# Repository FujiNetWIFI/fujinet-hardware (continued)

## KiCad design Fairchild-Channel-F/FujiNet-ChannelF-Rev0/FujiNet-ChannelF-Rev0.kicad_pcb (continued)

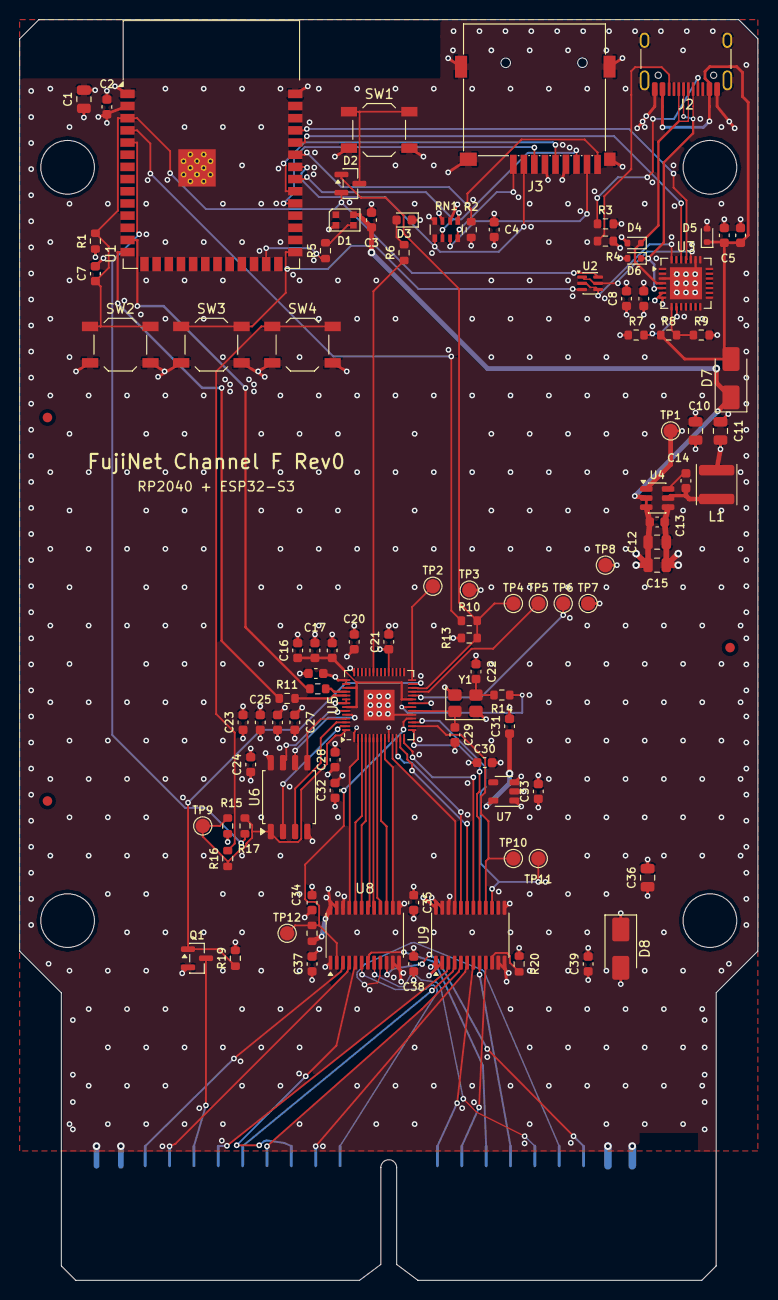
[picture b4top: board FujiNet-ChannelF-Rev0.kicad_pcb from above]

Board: 4 copper layers, 77.0 x 131.5 mm, 106 parts (0 on the bottom side), 87 nets.

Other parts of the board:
FID1, FID2, FID3: Fiducial_1mm_Mask2mm
H1, H2, H3, H4: MountingHole_5.6mm_NPTH

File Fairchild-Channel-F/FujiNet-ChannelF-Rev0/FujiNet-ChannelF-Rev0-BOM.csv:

"Qty","Refs","Value","Footprint","MPN","Manufacturer","LCSC","Description","DNP"
"6","C1,C10,C11,C12,C15,C36","22uF","C_0805_2012Metric","CL21A226MAQNNNE","Samsung Electro-Mechanics","C45783","capacitor (several uses: see schematic)",""
"22","C2,C3,C6,C9,C13,C14,C16,C17,C20,C21,C24,C25,C26,C27,C28,C31,C32,C34,C35,C37,C38,C39","100nF","C_0603_1608Metric","CC0603KRX7R9BB104","YAGEO","C14663","capacitor (several uses: see schematic)",""
"2","C4,C23","10uF","C_0603_1608Metric","CL10A106KP8NNNC","Samsung Electro-Mechanics","C19702","capacitor (several uses: see schematic)",""
"6","C5,C7,C18,C19,C30,C33","1uF","C_0603_1608Metric","CL10A105KB8NNNC","Samsung Electro-Mechanics","C15849","capacitor (several uses: see schematic)",""
"1","C8","4.7uF","C_0603_1608Metric","CL10A475KO8NNNC","Samsung Electro-Mechanics","C19666","CP2102N VDD bulk",""
"2","C22,C29","15pF","C_0603_1608Metric","CL10C150JB8NNNC","Samsung Electro-Mechanics","C1644","crystal load",""
"1","D1","WS2812B-2020-V6","LED_WS2812B-2020_PLCC4_2.0x2.0mm","WS2812B-2020-V6","Worldsemi","C52917434","status LED on +5V (datasheet VDD 3.7-5.3 V; VIH 2.7 V takes 3.3 V data)",""
"1","D2","BAT54C","SOT-23","BAT54C,215","Nexperia","C37704","RESET steering, common cathode",""
"1","D3","green","LED_0603_1608Metric","KT-0603G","Hubei KENTO Elec","C12624","RP activity LED",""
"3","D4,D5,D6","ESD5Z5.0T1G","D_SOD-523","ESD5Z5.0T1G","onsemi","C82044","ESD",""
"2","D7,D8","SS34","D_SMA","SS34","MDD (Microdiode Semiconductor)","C8678","diode (several uses: see schematic)",""
"1","J2","USB-C","USB_C_Receptacle_HRO_TYPE-C-31-M-12","TYPE-C-31-M-12","Korean Hroparts Elec","C165948","power + S3 programming",""
"1","J3","microSD","TF-SMD_TF-015","TF-015","SOFNG","C113206","microSD push-push, SPI mode",""
"1","L1","6.8uH","L_Sunlord_SWPA4030S","SWPA4030S6R8MT","Sunlord","C62684","buck inductor",""
"1","Q1","2N7002","SOT-23","2N7002","Jiangsu Changjing (JSCJ)","C8545","/INTREQ open-drain driver (GP16, unused by the firmware)",""
"6","R1,R2,R7,R13,R15,R20","10k","R_0603_1608Metric","0603WAF1002T5E","UNI-ROYAL","C25804","resistor (several uses: see schematic)",""
"2","R3,R4","5.1k","R_0603_1608Metric","0603WAF5101T5E","UNI-ROYAL","C23186","UFP Rd",""
"2","R5,R6","330R","R_0603_1608Metric","0603WAF3300T5E","UNI-ROYAL","C23138","resistor (several uses: see schematic)",""
"1","R8","22k","R_0603_1608Metric","0603WAF2202T5E","UNI-ROYAL","C31850","VBUS sense divider",""
"1","R9","47k","R_0603_1608Metric","0603WAF4702T5E","UNI-ROYAL","C25819","VBUS sense divider",""
"4","R10,R14,R16,R17","1k","R_0603_1608Metric","0603WAF1001T5E","UNI-ROYAL","C21190","resistor (several uses: see schematic)",""
"2","R11,R12","27R","R_0603_1608Metric","0603WAF270JT5E","UNI-ROYAL","C25190","USB series",""
"1","R18","4.7k","R_0603_1608Metric","0603WAF4701T5E","UNI-ROYAL","C23162","DIR pull-up: console -> cart through RP reset / boot",""
"1","R19","100k","R_0603_1608Metric","0603WAF1003T5E","UNI-ROYAL","C25803","/INTREQ FET gate pull-down",""
"1","RN1","4x10k","R_Array_Convex_4x0603","4D03WGJ0103T5E","UNI-ROYAL","C29718","SD pull-ups",""
"1","SW1","RESET","SW_SPST_TL3342","TL3342F160QG","E-Switch","C2886898","cart RESET: RP RUN + S3 EN via BAT54C",""
"1","SW2","S3_RST","SW_SPST_TL3342","TL3342F160QG","E-Switch","C2886898","ESP32-S3 EN",""
"1","SW3","S3_BOOT","SW_SPST_TL3342","TL3342F160QG","E-Switch","C2886898","ESP32-S3 BOOT (IO0)",""
"1","SW4","BOOTSEL","SW_SPST_TL3342","TL3342F160QG","E-Switch","C2886898","RP2040 BOOTSEL (hold while pressing RESET)",""
"1","U1","ESP32-S3-WROOM-1-N16R8","ESP32-S3-WROOM-1","ESP32-S3-WROOM-1-N16R8","Espressif","C2913202","FujiNet core (fujiversal-channelf)",""
"1","U2","UMH3N","SOT-363_SC-70-6","UMH3N","Jiangsu Changjing (JSCJ)","C62892","esptool auto-program (DevKitC-1 style)",""
"1","U3","CP2102N-A02-GQFN28","QFN-28-1EP_5x5mm_P0.5mm_EP3.35x3.35mm","CP2102N-A02-GQFN28R","Silicon Labs","C964632","USB-UART for S3 flashing/console (self-powered)",""
"1","U4","AP63203WU","TSOT-23-6","AP63203WU-7","Diodes Incorporated","C780769","3.3V 2A buck",""
"1","U5","RP2040","QFN-56-1EP_7x7mm_P0.4mm_EP3.2x3.2mm","RP2040","Raspberry Pi","C2040","F8 bus memory device: ROMC state machine on core1 (fujichannelf)",""
"1","U6","W25Q16JVSSIQ","SOIC-8_5.3x5.3mm_P1.27mm","W25Q16JVSSIQ","Winbond","C82317","2 MB QSPI boot flash",""
"1","U7","AP2112K-3.3","SOT-23-5","AP2112K-3.3TRG1","Diodes Incorporated","C51118","RP2040 + flash + translator B ports 3.3V LDO, fast start",""
"2","U8,U9","SN74LVC4245APWR","TSSOP-24_4.4x7.8mm_P0.65mm","SN74LVC4245APWR","Texas Instruments","C7859","U (several uses: see schematic)",""
"1","Y1","12MHz","Crystal_SMD_3225-4Pin_3.2x2.5mm","ABM8-272-T3","Abracon","C20625731","",""

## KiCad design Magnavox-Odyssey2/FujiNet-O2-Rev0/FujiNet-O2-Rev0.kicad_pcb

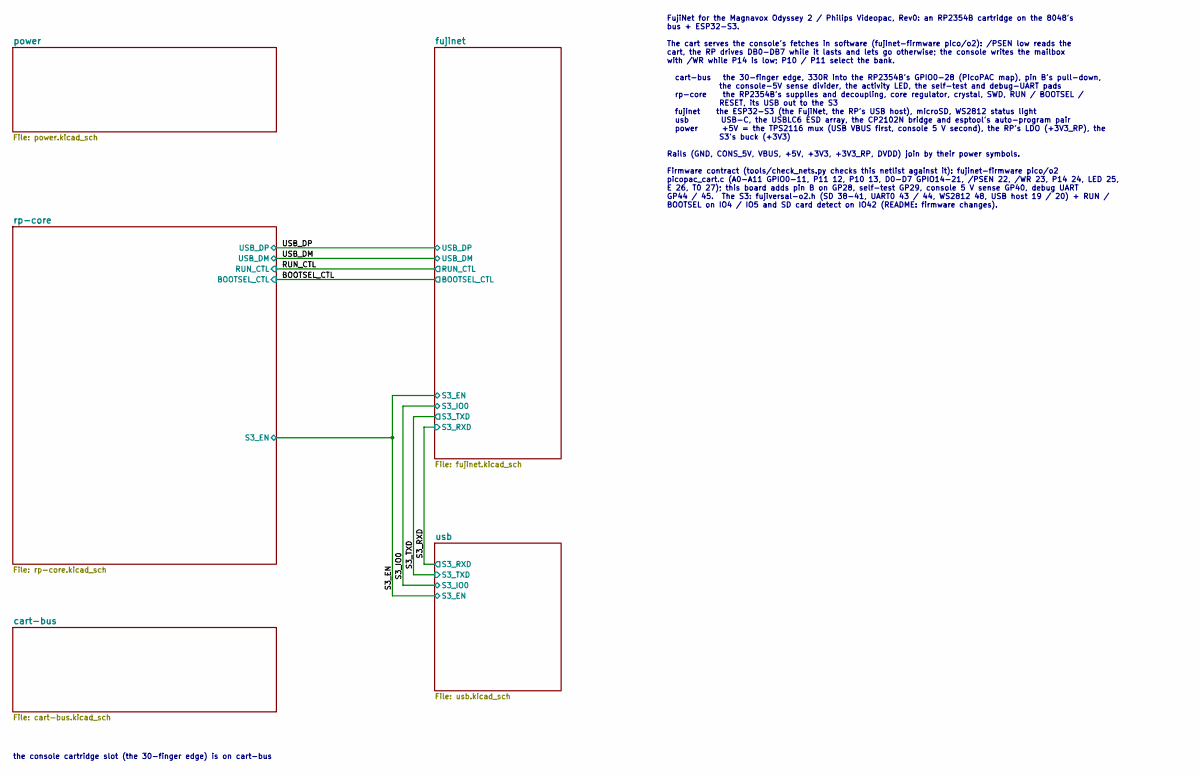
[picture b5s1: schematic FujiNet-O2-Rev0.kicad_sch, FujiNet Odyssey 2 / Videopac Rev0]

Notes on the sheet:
the console cartridge slot (the 30-finger edge) is on cart-bus
FujiNet for the Magnavox Odyssey 2 / Philips Videopac, Rev0: an RP2354B cartridge on the 8048's bus + ESP32-S3. The cart serves the console's fetches in software (fujinet-firmware pico/o2): /PSEN low reads the cart, the RP drives DB0-DB7 while it lasts and lets go otherwise; the console writes the 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

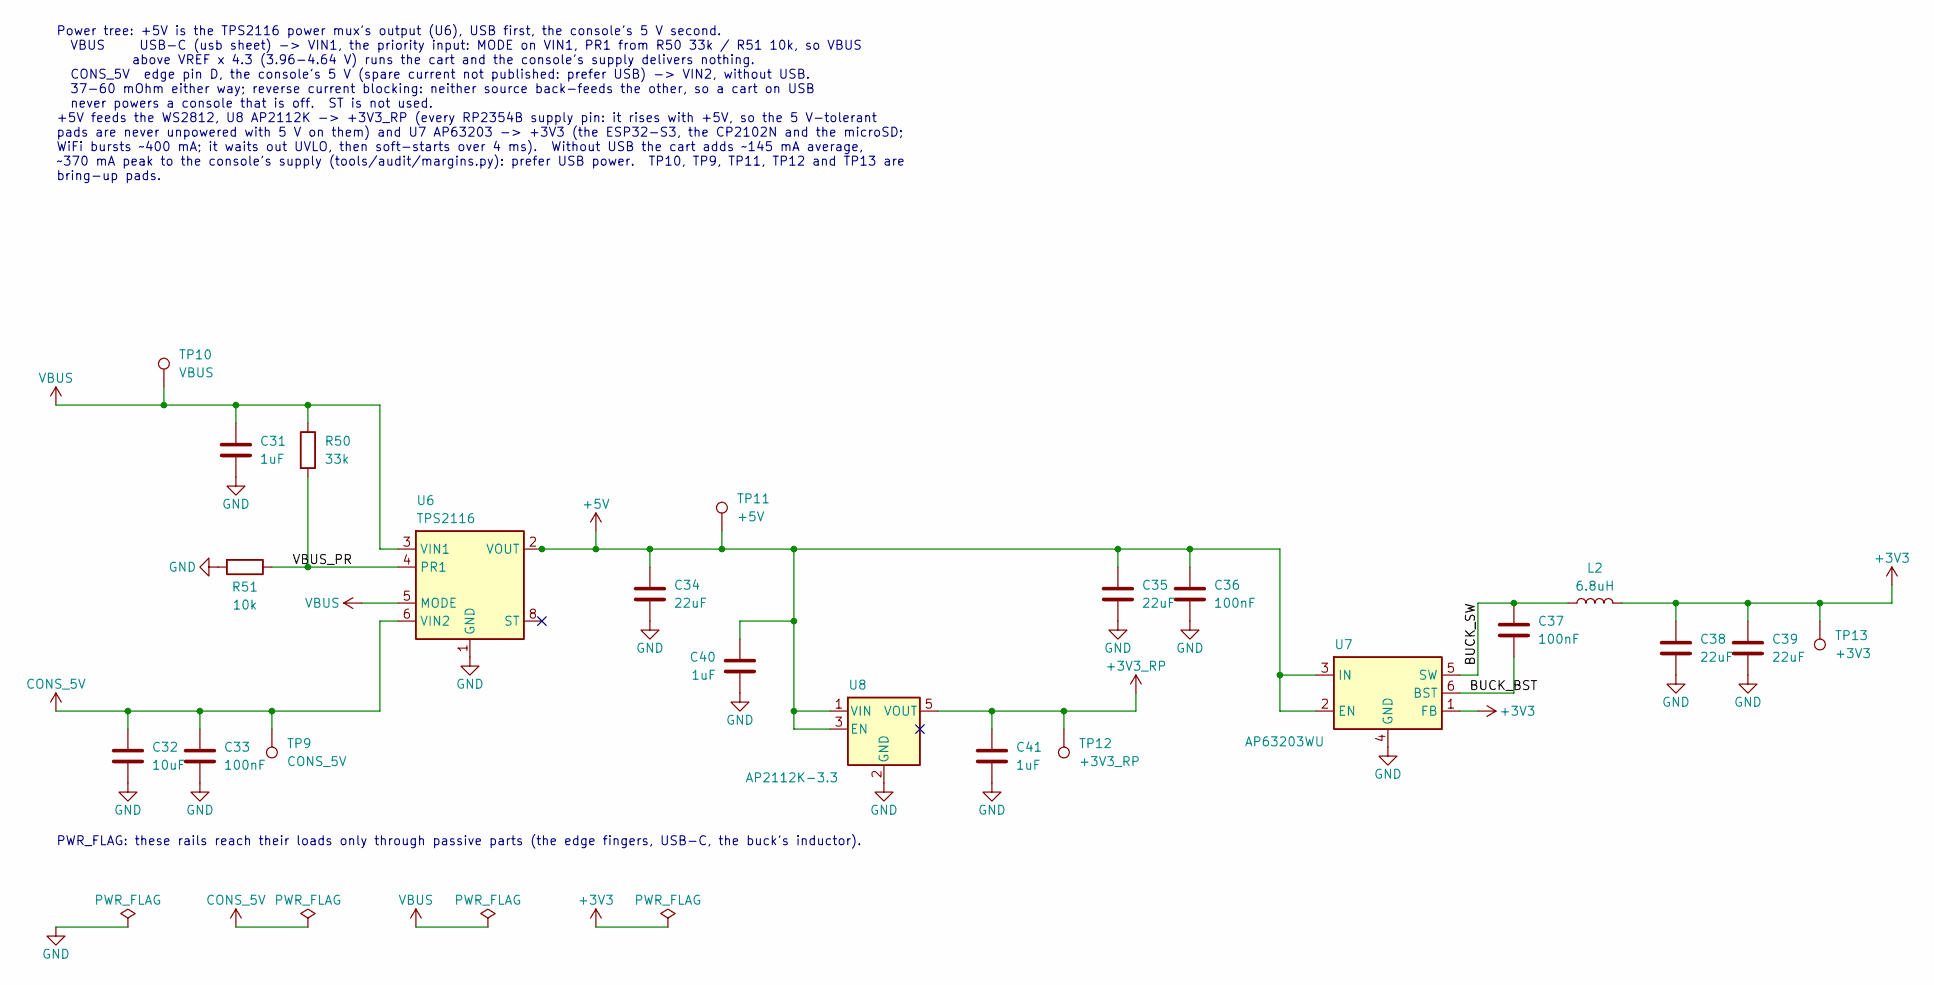
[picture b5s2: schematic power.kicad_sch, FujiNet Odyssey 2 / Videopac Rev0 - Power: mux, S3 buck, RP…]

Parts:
C31, C40, C41: 1uF; C_0603_1608Metric; MPN CL10A105KB8NNNC; LCSC C15849
C32: 10uF; C_0603_1608Metric; MPN CL10A106KP8NNNC; LCSC C19702
C33, C36, C37: 100nF; C_0603_1608Metric; MPN CC0603KRX7R9BB104; LCSC C14663
C34, C35, C38, C39: 22uF; C_0805_2012Metric; MPN CL21A226MAQNNNE; LCSC C45783
L2: 6.8uH; L_Sunlord_SWPA4030S; MPN SWPA4030S6R8MT; LCSC C62684
R50: 33k; R_0603_1608Metric; MPN 0603WAF3302T5E; LCSC C4216
R51: 10k; R_0603_1608Metric; MPN 0603WAF1002T5E; LCSC C25804
TP9: CONS_5V; TestPoint_Pad_D1.5mm
TP10: VBUS; TestPoint_Pad_D1.5mm
TP11: +5V; TestPoint_Pad_D1.5mm
TP12: +3V3_RP; TestPoint_Pad_D1.5mm
TP13: +3V3; TestPoint_Pad_D1.5mm
U6: TPS2116; SOT-583-8; MPN TPS2116DRLR; LCSC C3235557
U7: AP63203WU; TSOT-23-6; MPN AP63203WU-7; LCSC C780769
U8: AP2112K-3.3; SOT-23-5; MPN AP2112K-3.3TRG1; LCSC C51118

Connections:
+3V3: C38.1, C39.1, L2.2, TP13.1, U7.1 (FB); also elsewhere on the board
+3V3_RP: C41.1, TP12.1, U8.5 (VOUT); also elsewhere on the board
+5V: C34.1, C35.1, C36.1, C40.1, TP11.1, U6.2 (VOUT), U6.7 (VOUT), U7.2 (EN), U7.3 (IN), U8.1 (VIN), U8.3 (EN); also elsewhere on the board
/power/BUCK_BST: C37.2, U7.6 (BST)
/power/BUCK_SW: C37.1, L2.1, U7.5 (SW)
/power/VBUS_PR: R50.2, R51.1, U6.4 (PR1)
CONS_5V: C32.1, C33.1, TP9.1, U6.6 (VIN2); also elsewhere on the board
GND: C31.2, C32.2, C33.2, C34.2, C35.2, C36.2, C38.2, C39.2, C40.2, C41.2, R51.2, U6.1 (GND), U7.4 (GND), U8.2 (GND); also elsewhere on the board
VBUS: C31.1, R50.1, TP10.1, U6.3 (VIN1), U6.5 (MODE); also elsewhere on the board

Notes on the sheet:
PWR_FLAG: these rails reach their loads only through passive parts (the edge fingers, USB-C, the buck's inductor).
Power tree: +5V is the TPS2116 power mux's output (U6), USB first, the console's 5 V second. VBUS USB-C (usb sheet) -> VIN1, the priority input: MODE on VIN1, PR1 from R50 33k / R51 10k, so VBUS above VREF x 4.3 (3.96-4.64 V) runs the cart and the console's supply delivers nothing. CONS_5V edge pin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

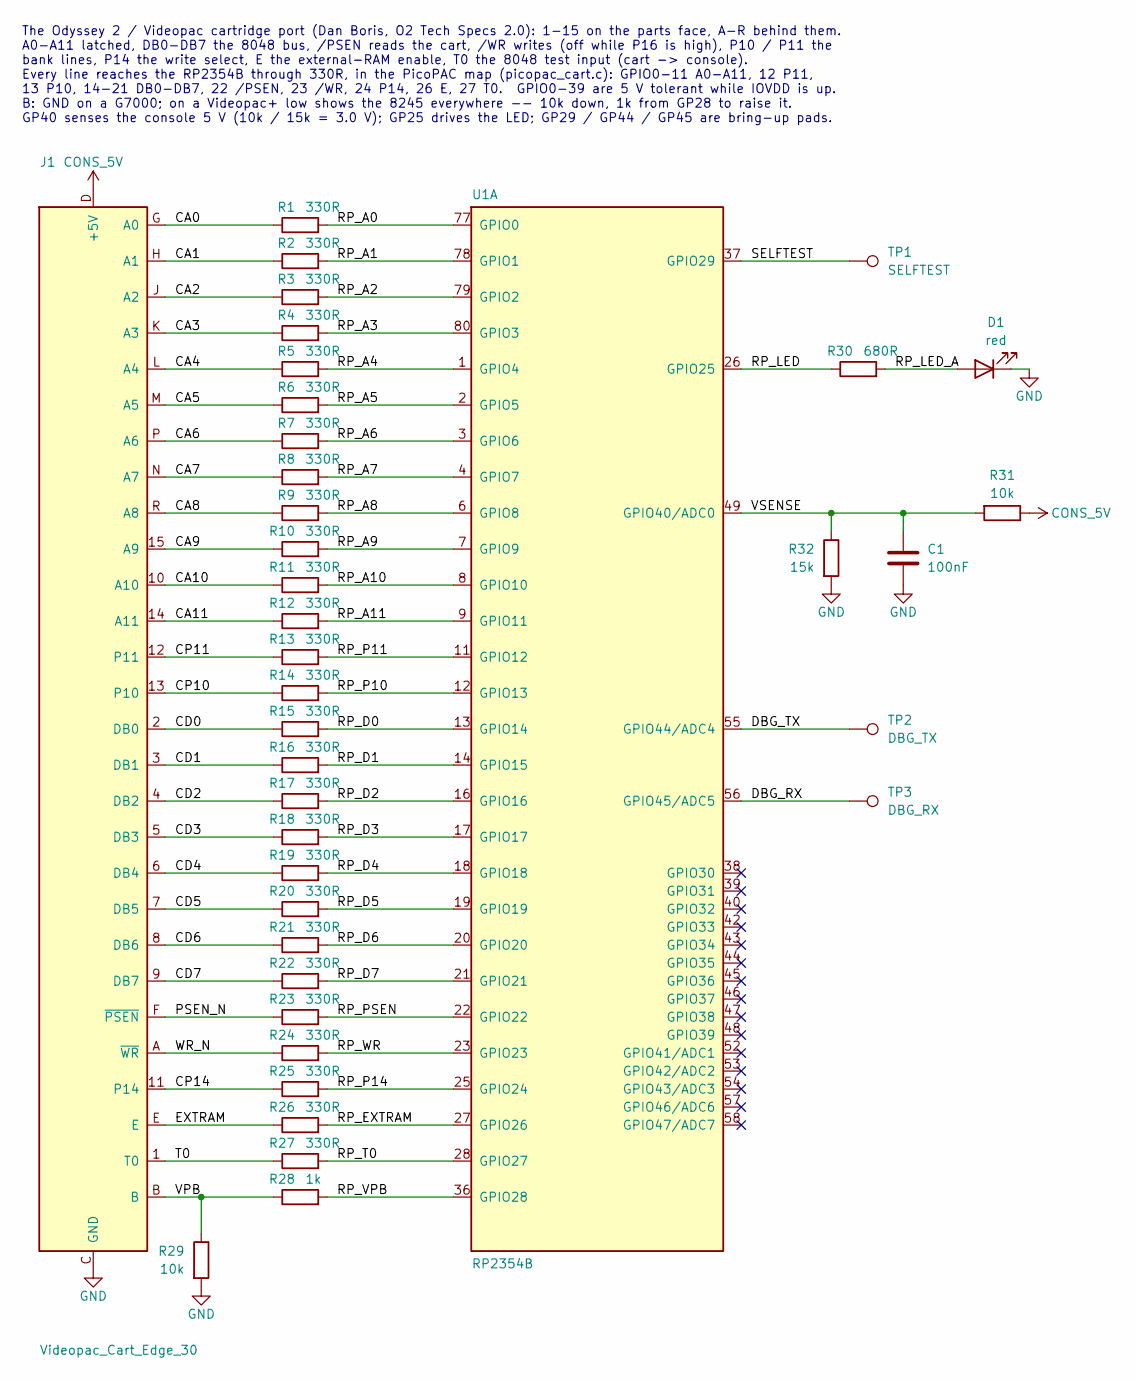
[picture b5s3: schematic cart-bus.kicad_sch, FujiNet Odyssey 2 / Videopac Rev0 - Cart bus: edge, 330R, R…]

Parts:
C1: 100nF; C_0603_1608Metric; MPN CC0603KRX7R9BB104; LCSC C14663
D1: red; LED_0603_1608Metric; MPN KT-0603R; LCSC C2286
J1: Videopac_Cart_Edge_30
R1, R2, R3, R4, R5, R6, R7, R8, R9, R10, R11, R12, R13, R14, R15, R16, R17, R18, R19, R20, R21, R22, R23, R24, R25, R26, R27: 330R; R_0603_1608Metric; MPN 0603WAF3300T5E; LCSC C23138
R28: 1k; R_0603_1608Metric; MPN 0603WAF1001T5E; LCSC C21190
R29, R31: 10k; R_0603_1608Metric; MPN 0603WAF1002T5E; LCSC C25804
R30: 680R; R_0603_1608Metric; MPN 0603WAF6800T5E; LCSC C23228
R32: 15k; R_0603_1608Metric; MPN 0603WAF1502T5E; LCSC C22809
TP1: SELFTEST; TestPoint_Pad_D1.5mm
TP2: DBG_TX; TestPoint_Pad_D1.5mm
TP3: DBG_RX; TestPoint_Pad_D1.5mm
U1: RP2354B; QFN-80-1EP_10x10mm_P0.4mm_EP3.4x3.4mm; MPN RP2354B; LCSC C39843328

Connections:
/cart-bus/CA0: J1.G (A0), R1.1
/cart-bus/CA1: J1.H (A1), R2.1
/cart-bus/CA2: J1.J (A2), R3.1
/cart-bus/CA3: J1.K (A3), R4.1
/cart-bus/CA4: J1.L (A4), R5.1
/cart-bus/CA5: J1.M (A5), R6.1
/cart-bus/CA6: J1.P (A6), R7.1
/cart-bus/CA7: J1.N (A7), R8.1
/cart-bus/CA8: J1.R (A8), R9.1
/cart-bus/CA9: J1.15 (A9), R10.1
/cart-bus/CA10: J1.10 (A10), R11.1
/cart-bus/CA11: J1.14 (A11), R12.1
/cart-bus/CD0: J1.2 (DB0), R15.1
/cart-bus/CD1: J1.3 (DB1), R16.1
/cart-bus/CD2: J1.4 (DB2), R17.1
/cart-bus/CD3: J1.5 (DB3), R18.1
/cart-bus/CD4: J1.6 (DB4), R19.1
/cart-bus/CD5: J1.7 (DB5), R20.1
/cart-bus/CD6: J1.8 (DB6), R21.1
/cart-bus/CD7: J1.9 (DB7), R22.1
/cart-bus/CP10: J1.13 (P10), R14.1
/cart-bus/CP11: J1.12 (P11), R13.1
/cart-bus/CP14: J1.11 (P14), R25.1
/cart-bus/DBG_RX: TP3.1, U1.56 (GPIO45/ADC5)
/cart-bus/DBG_TX: TP2.1, U1.55 (GPIO44/ADC4)
/cart-bus/EXTRAM: J1.E, R26.1
/cart-bus/PSEN_N: J1.F (~PSEN), R23.1
/cart-bus/RP_A0: R1.2, U1.77 (GPIO0)
/cart-bus/RP_A1: R2.2, U1.78 (GPIO1)
/cart-bus/RP_A2: R3.2, U1.79 (GPIO2)
/cart-bus/RP_A3: R4.2, U1.80 (GPIO3)
/cart-bus/RP_A4: R5.2, U1.1 (GPIO4)
/cart-bus/RP_A5: R6.2, U1.2 (GPIO5)
/cart-bus/RP_A6: R7.2, U1.3 (GPIO6)
/cart-bus/RP_A7: R8.2, U1.4 (GPIO7)
/cart-bus/RP_A8: R9.2, U1.6 (GPIO8)
/cart-bus/RP_A9: R10.2, U1.7 (GPIO9)
/cart-bus/RP_A10: R11.2, U1.8 (GPIO10)
/cart-bus/RP_A11: R12.2, U1.9 (GPIO11)
/cart-bus/RP_D0: R15.2, U1.13 (GPIO14)
/cart-bus/RP_D1: R16.2, U1.14 (GPIO15)
/cart-bus/RP_D2: R17.2, U1.16 (GPIO16)
/cart-bus/RP_D3: R18.2, U1.17 (GPIO17)
/cart-bus/RP_D4: R19.2, U1.18 (GPIO18)
/cart-bus/RP_D5: R20.2, U1.19 (GPIO19)
/cart-bus/RP_D6: R21.2, U1.20 (GPIO20)
/cart-bus/RP_D7: R22.2, U1.21 (GPIO21)
/cart-bus/RP_EXTRAM: R26.2, U1.27 (GPIO26)
/cart-bus/RP_LED: R30.1, U1.26 (GPIO25)
/cart-bus/RP_LED_A: D1.2 (A), R30.2
/cart-bus/RP_P10: R14.2, U1.12 (GPIO13)
/cart-bus/RP_P11: R13.2, U1.11 (GPIO12)
/cart-bus/RP_P14: R25.2, U1.25 (GPIO24)
/cart-bus/RP_PSEN: R23.2, U1.22 (GPIO22)
/cart-bus/RP_T0: R27.2, U1.28 (GPIO27)
/cart-bus/RP_VPB: R28.2, U1.36 (GPIO28)
/cart-bus/RP_WR: R24.2, U1.23 (GPIO23)
/cart-bus/SELFTEST: TP1.1, U1.37 (GPIO29)
/cart-bus/T0: J1.1 (T0), R27.1
/cart-bus/VPB: J1.B, R28.1, R29.1
/cart-bus/VSENSE: C1.1, R31.2, R32.1, U1.49 (GPIO40/ADC0)
/cart-bus/WR_N: J1.A (~WR), R24.1
CONS_5V: J1.D (+5V), R31.1; also elsewhere on the board
GND: C1.2, D1.1 (K), J1.C (GND), R29.2, R32.2; also elsewhere on the board

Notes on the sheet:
The Odyssey 2 / Videopac cartridge port (Dan Boris, O2 Tech Specs 2.0): 1-15 on the parts face, A-R behind them. A0-A11 latched, DB0-DB7 the 8048 bus, /PSEN reads the cart, /WR writes (off while P16 is high), P10 / P11 the bank lines, P14 the write select, E the external-RAM enable, T0 the 8048 tes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

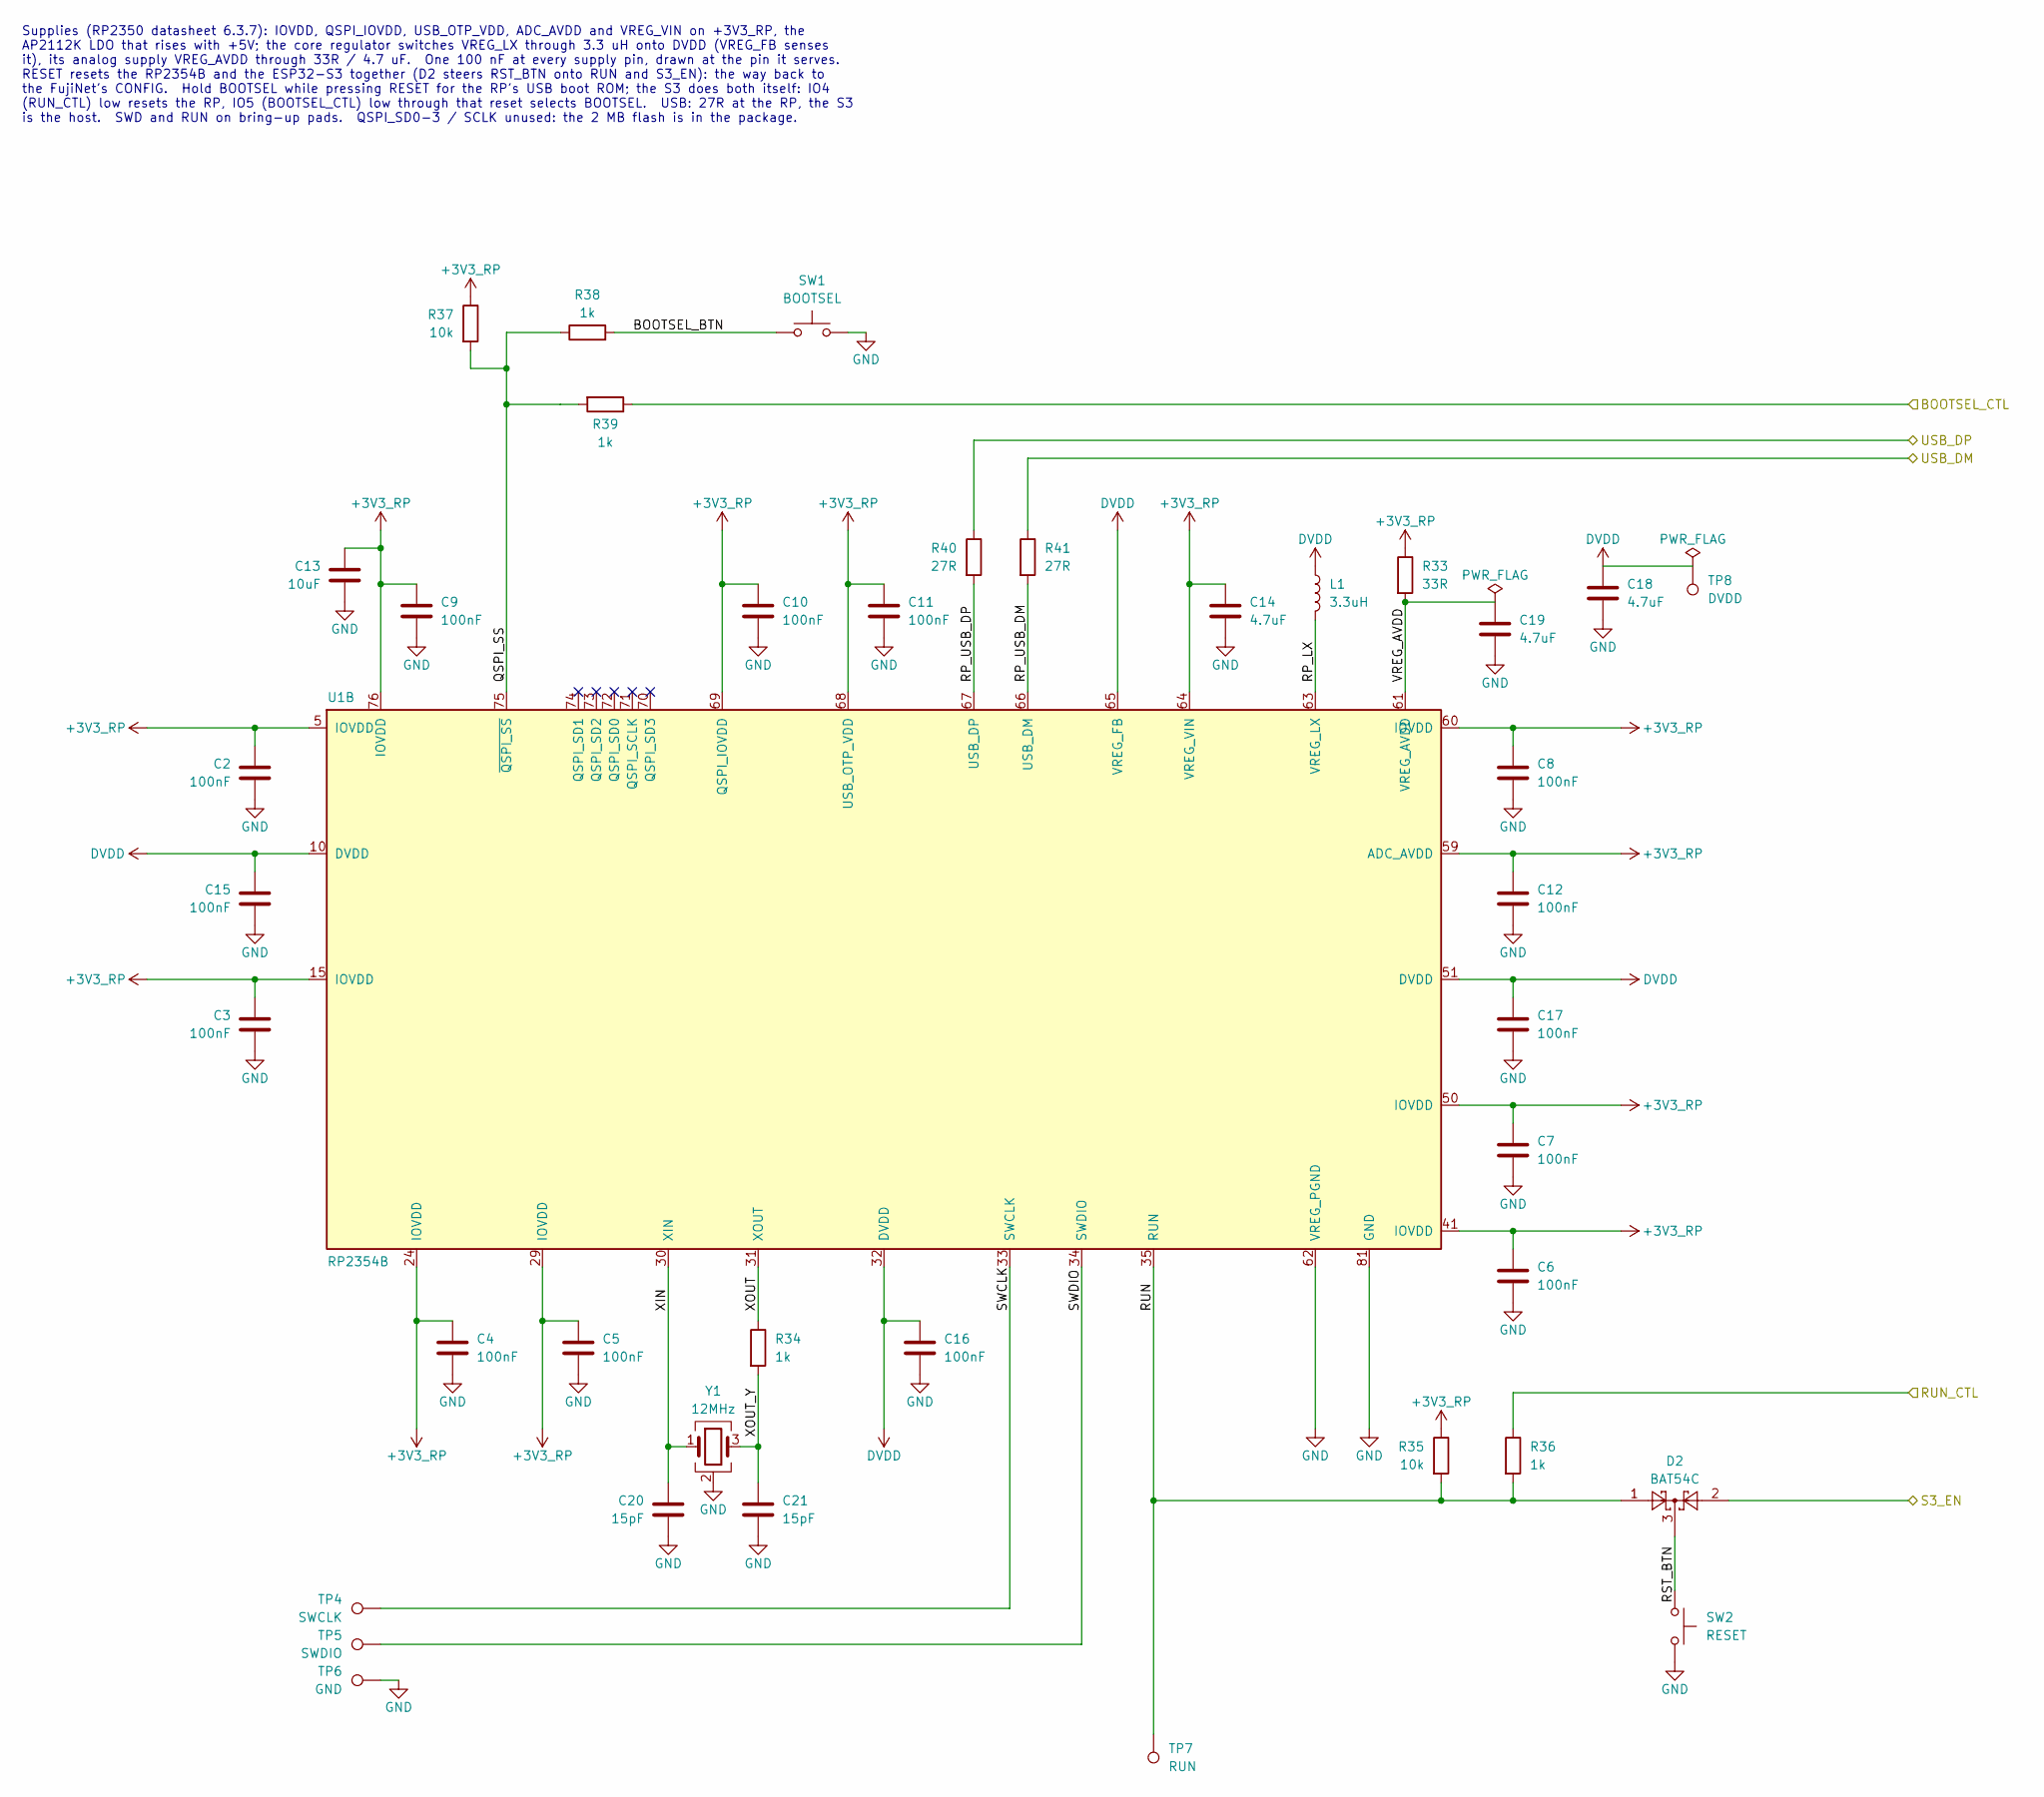
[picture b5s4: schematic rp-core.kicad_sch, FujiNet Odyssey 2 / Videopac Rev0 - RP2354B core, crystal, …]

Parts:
C2, C3, C4, C5, C6, C8, C9, C10, C12, C15, C16: 100nF; C_0603_1608Metric; MPN CC0603KRX7R9BB104; LCSC C14663
C7, C11, C17: 100nF; RPI_C0402; MPN CL05B104KO5NNNC; LCSC C1525
C13: 10uF; C_0603_1608Metric; MPN CL10A106KP8NNNC; LCSC C19702
C14, C18: 4.7uF; RPI_C0402_wide; MPN CL05A475MP5NRNC; LCSC C23733
C19: 4.7uF; RPI_C0402; MPN CL05A475MP5NRNC; LCSC C23733
C20, C21: 15pF; C_0603_1608Metric; MPN CL10C150JB8NNNC; LCSC C1644
D2: BAT54C; SOT-23; MPN BAT54C,215; LCSC C37704
L1: 3.3uH; RPI_L_AOTA-B201610S3R3; MPN AOTA-B201610S3R3-101-T; LCSC C42411119
R33: 33R; RPI_R0402; MPN 0402WGF330JTCE; LCSC C25105
R34, R36, R38, R39: 1k; R_0603_1608Metric; MPN 0603WAF1001T5E; LCSC C21190
R35, R37: 10k; R_0603_1608Metric; MPN 0603WAF1002T5E; LCSC C25804
R40, R41: 27R; RPI_R0402; MPN 0402WGF270JTCE; LCSC C25100
SW1: BOOTSEL; SW_SPST_TS-1187A; MPN TS-1187A-B-A-B; LCSC C318884
SW2: RESET; SW_SPST_TS-1187A; MPN TS-1187A-B-A-B; LCSC C318884
TP4: SWCLK; TestPoint_Pad_D1.5mm
TP5: SWDIO; TestPoint_Pad_D1.5mm
TP6: GND; TestPoint_Pad_D1.5mm
TP7: RUN; TestPoint_Pad_D1.5mm
TP8: DVDD; TestPoint_Pad_D1.5mm
U1: RP2354B; QFN-80-1EP_10x10mm_P0.4mm_EP3.4x3.4mm; MPN RP2354B; LCSC C39843328
Y1: 12MHz; Crystal_SMD_3225-4Pin_3.2x2.5mm; MPN ABM8-272-T3; LCSC C20625731

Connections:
+3V3_RP: C2.1, C3.1, C4.1, C5.1, C6.1, C7.1, C8.1, C9.1, C10.1, C11.1, C12.1, C13.1, C14.1, R33.1, R35.1, R37.1, U1.5 (IOVDD), U1.15 (IOVDD), U1.24 (IOVDD), U1.29 (IOVDD), U1.41 (IOVDD), U1.50 (IOVDD), U1.59 (ADC_AVDD), U1.60 (IOVDD), U1.64 (VREG_VIN), U1.68 (USB_OTP_VDD), U1.69 (QSPI_IOVDD), U1.76 (IOVDD); also elsewhere on the board
/BOOTSEL_CTL: R39.1; also elsewhere on the board
/RUN_CTL: R36.1; also elsewhere on the board
/S3_EN: D2.2; also elsewhere on the board
/USB_DM: R41.1; also elsewhere on the board
/USB_DP: R40.1; also elsewhere on the board
/rp-core/BOOTSEL_BTN: R38.2, SW1.1
/rp-core/QSPI_SS: R37.2, R38.1, R39.2, U1.75 (~QSPI_SS)
/rp-core/RP_LX: L1.2, U1.63 (VREG_LX)
/rp-core/RP_USB_DM: R41.2, U1.66 (USB_DM)
/rp-core/RP_USB_DP: R40.2, U1.67 (USB_DP)
/rp-core/RST_BTN: D2.3, SW2.1
/rp-core/RUN: D2.1, R35.2, R36.2, TP7.1, U1.35 (RUN)
/rp-core/SWCLK: TP4.1, U1.33 (SWCLK)
/rp-core/SWDIO: TP5.1, U1.34 (SWDIO)
/rp-core/VREG_AVDD: C19.1, R33.2, U1.61 (VREG_AVDD)
/rp-core/XIN: C20.1, U1.30 (XIN), Y1.1
/rp-core/XOUT: R34.1, U1.31 (XOUT)
/rp-core/XOUT_Y: C21.1, R34.2, Y1.3
DVDD: C15.1, C16.1, C17.1, C18.1, L1.1, TP8.1, U1.10 (DVDD), U1.32 (DVDD), U1.51 (DVDD), U1.65 (VREG_FB)
GND: C2.2, C3.2, C4.2, C5.2, C6.2, C7.2, C8.2, C9.2, C10.2, C11.2, C12.2, C13.2, C14.2, C15.2, C16.2, C17.2, C18.2, C19.2, C20.2, C21.2, SW1.2, SW2.2, TP6.1, U1.62 (VREG_PGND), U1.81 (GND), Y1.2 (G), Y1.4 (G); also elsewhere on the board

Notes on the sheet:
Supplies (RP2350 datasheet 6.3.7): IOVDD, QSPI_IOVDD, USB_OTP_VDD, ADC_AVDD and VREG_VIN on +3V3_RP, the AP2112K LDO that rises with +5V; the core regulator switches VREG_LX through 3.3 uH onto DVDD (VREG_FB senses it), its analog supply VREG_AVDD through 33R / 4.7 uF. One 100 nF at every supply pi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

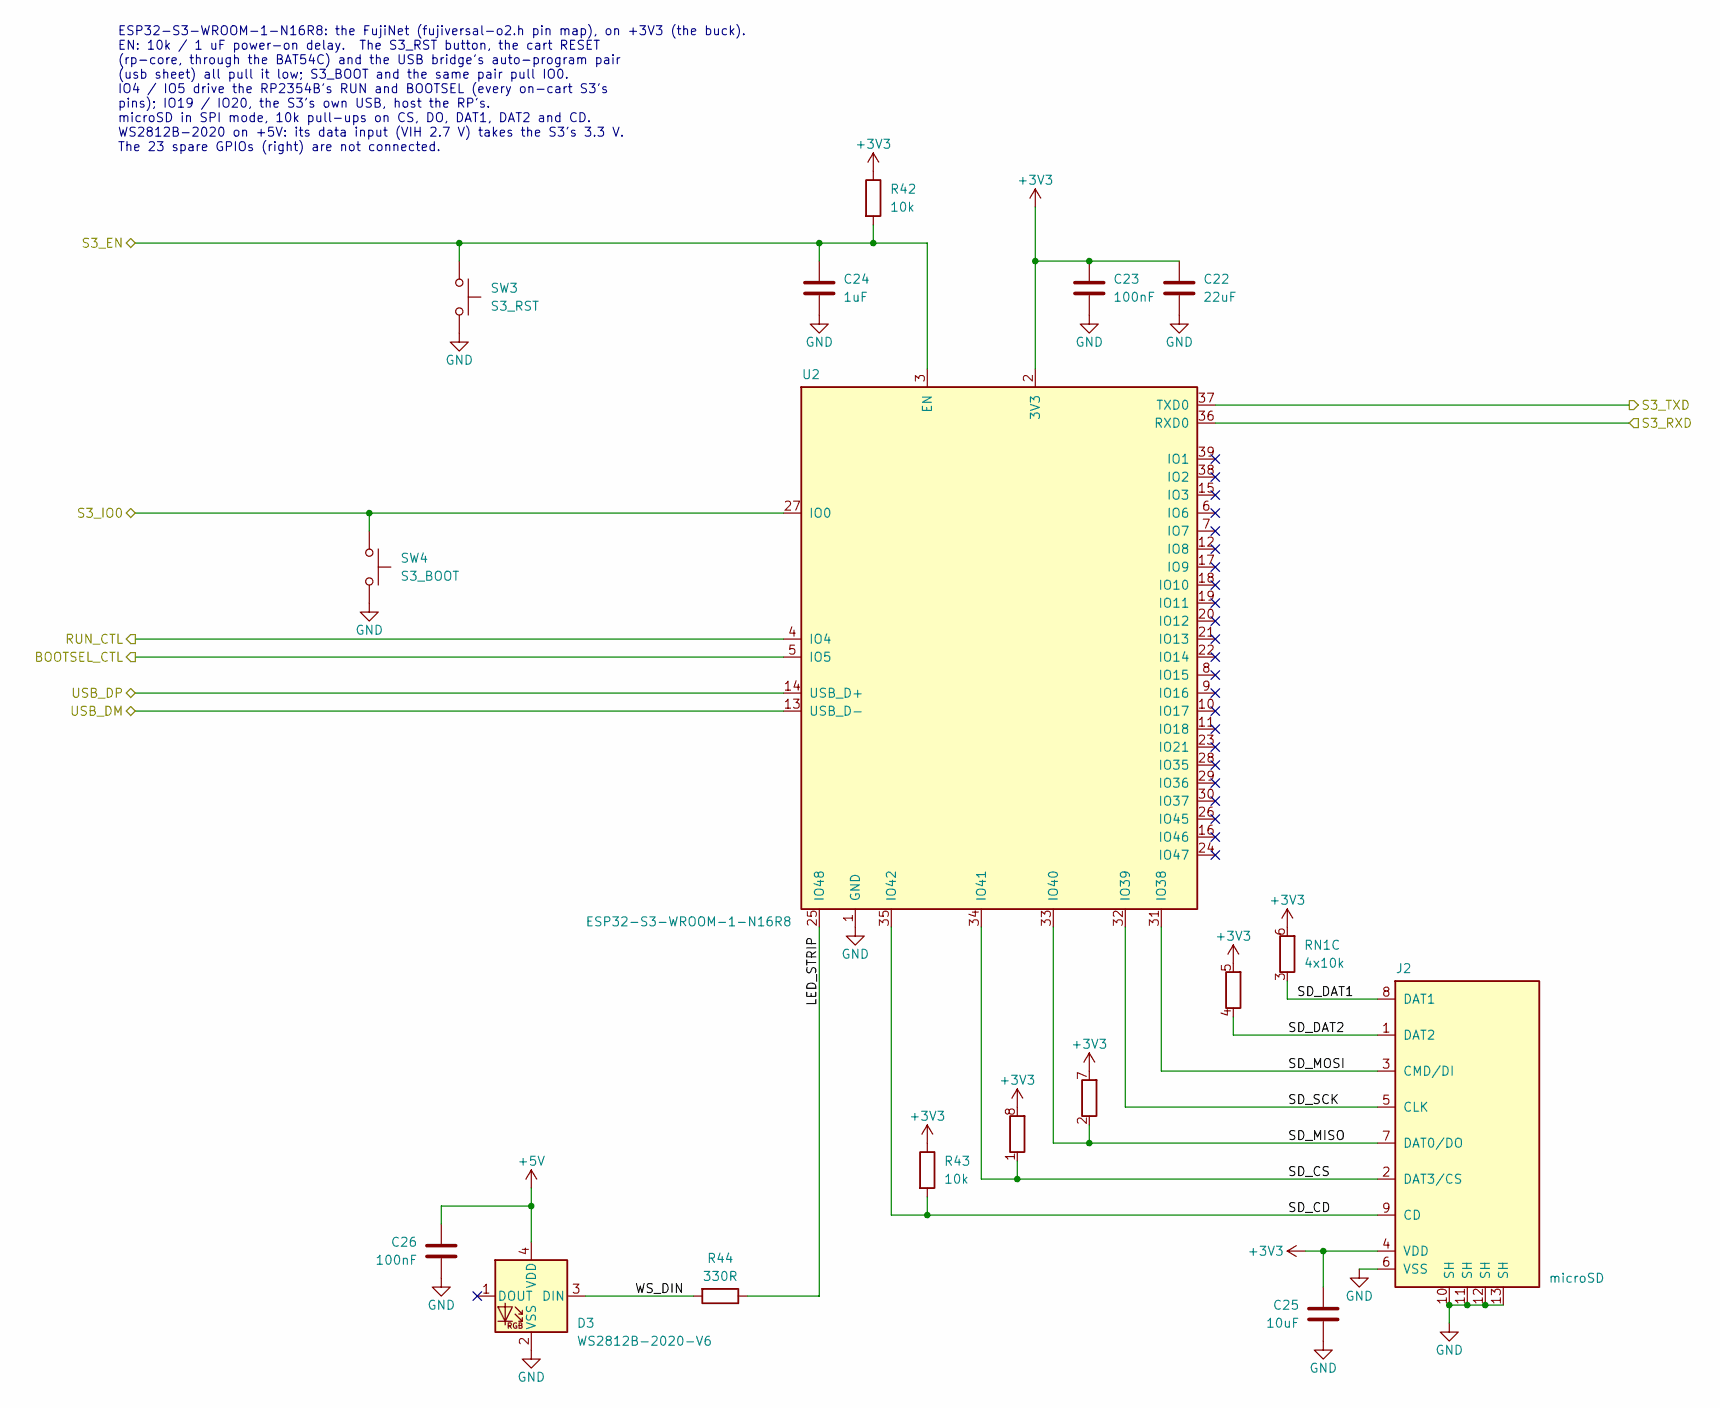
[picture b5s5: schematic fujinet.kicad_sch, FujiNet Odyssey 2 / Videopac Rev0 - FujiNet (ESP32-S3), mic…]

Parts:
C22: 22uF; C_0805_2012Metric; MPN CL21A226MAQNNNE; LCSC C45783
C23, C26: 100nF; C_0603_1608Metric; MPN CC0603KRX7R9BB104; LCSC C14663
C24: 1uF; C_0603_1608Metric; MPN CL10A105KB8NNNC; LCSC C15849
C25: 10uF; C_0603_1608Metric; MPN CL10A106KP8NNNC; LCSC C19702
D3: WS2812B-2020-V6; LED_WS2812B-2020_PLCC4_2.0x2.0mm; MPN WS2812B-2020-V6; LCSC C52917434
J2: microSD; TF-SMD_TF-015; MPN TF-015; LCSC C113206
R42, R43: 10k; R_0603_1608Metric; MPN 0603WAF1002T5E; LCSC C25804
R44: 330R; R_0603_1608Metric; MPN 0603WAF3300T5E; LCSC C23138
RN1: 4x10k; R_Array_Convex_4x0603; MPN 4D03WGJ0103T5E; LCSC C29718
SW3: S3_RST; SW_SPST_TS-1187A; MPN TS-1187A-B-A-B; LCSC C318884
SW4: S3_BOOT; SW_SPST_TS-1187A; MPN TS-1187A-B-A-B; LCSC C318884
U2: ESP32-S3-WROOM-1-N16R8; ESP32-S3-WROOM-1; MPN ESP32-S3-WROOM-1-N16R8; LCSC C2913202

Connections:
+3V3: C22.1, C23.1, C25.1, J2.4 (VDD), R42.1, R43.1, RN1.5 (R4.2), RN1.6 (R3.2), RN1.7 (R2.2), RN1.8 (R1.2), U2.2 (3V3); also elsewhere on the board
+5V: C26.1, D3.4 (VDD); also elsewhere on the board
/BOOTSEL_CTL: U2.5 (IO5); also elsewhere on the board
/RUN_CTL: U2.4 (IO4); also elsewhere on the board
/S3_EN: C24.1, R42.2, SW3.1, U2.3 (EN); also elsewhere on the board
/S3_IO0: SW4.1, U2.27 (IO0); also elsewhere on the board
/S3_RXD: U2.36 (RXD0); also elsewhere on the board
/S3_TXD: U2.37 (TXD0); also elsewhere on the board
/USB_DM: U2.13 (USB_D-); also elsewhere on the board
/USB_DP: U2.14 (USB_D+); also elsewhere on the board
/fujinet/LED_STRIP: R44.1, U2.25 (IO48)
/fujinet/SD_CD: J2.9 (CD), R43.2, U2.35 (IO42)
/fujinet/SD_CS: J2.2 (DAT3/CS), RN1.1 (R1.1), U2.34 (IO41)
/fujinet/SD_DAT1: J2.8 (DAT1), RN1.3 (R3.1)
/fujinet/SD_DAT2: J2.1 (DAT2), RN1.4 (R4.1)
/fujinet/SD_MISO: J2.7 (DAT0/DO), RN1.2 (R2.1), U2.33 (IO40)
/fujinet/SD_MOSI: J2.3 (CMD/DI), U2.31 (IO38)
/fujinet/SD_SCK: J2.5 (CLK), U2.32 (IO39)
/fujinet/WS_DIN: D3.3 (DIN), R44.2
GND: C22.2, C23.2, C24.2, C25.2, C26.2, D3.2 (VSS), J2.6 (VSS), J2.10 (SH), J2.11 (SH), J2.12 (SH), J2.13 (SH), SW3.2, SW4.2, U2.1 (GND), U2.40 (GND), U2.41 (GND); also elsewhere on the board

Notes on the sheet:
ESP32-S3-WROOM-1-N16R8: the FujiNet (fujiversal-o2.h pin map), on +3V3 (the buck). EN: 10k / 1 uF power-on delay. The S3_RST button, the cart RESET (rp-core, through the BAT54C) and the USB bridge's auto-program pair (usb sheet) all pull it low; S3_BOOT and the same pair pull IO0. IO4 / IO5 drive t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
